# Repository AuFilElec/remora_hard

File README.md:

# remora_hard
PCB Remora v1.4 - gestionnaire de chauffage électrique

La **Remora** permet de piloter 7 zones de chauffage électrique via les fils pilotes. Mais aussi de récupérer la téléinformation de votre compteur Enedis et piloter votre ballon d'eau chaude.

**Schematic**

**PCB**

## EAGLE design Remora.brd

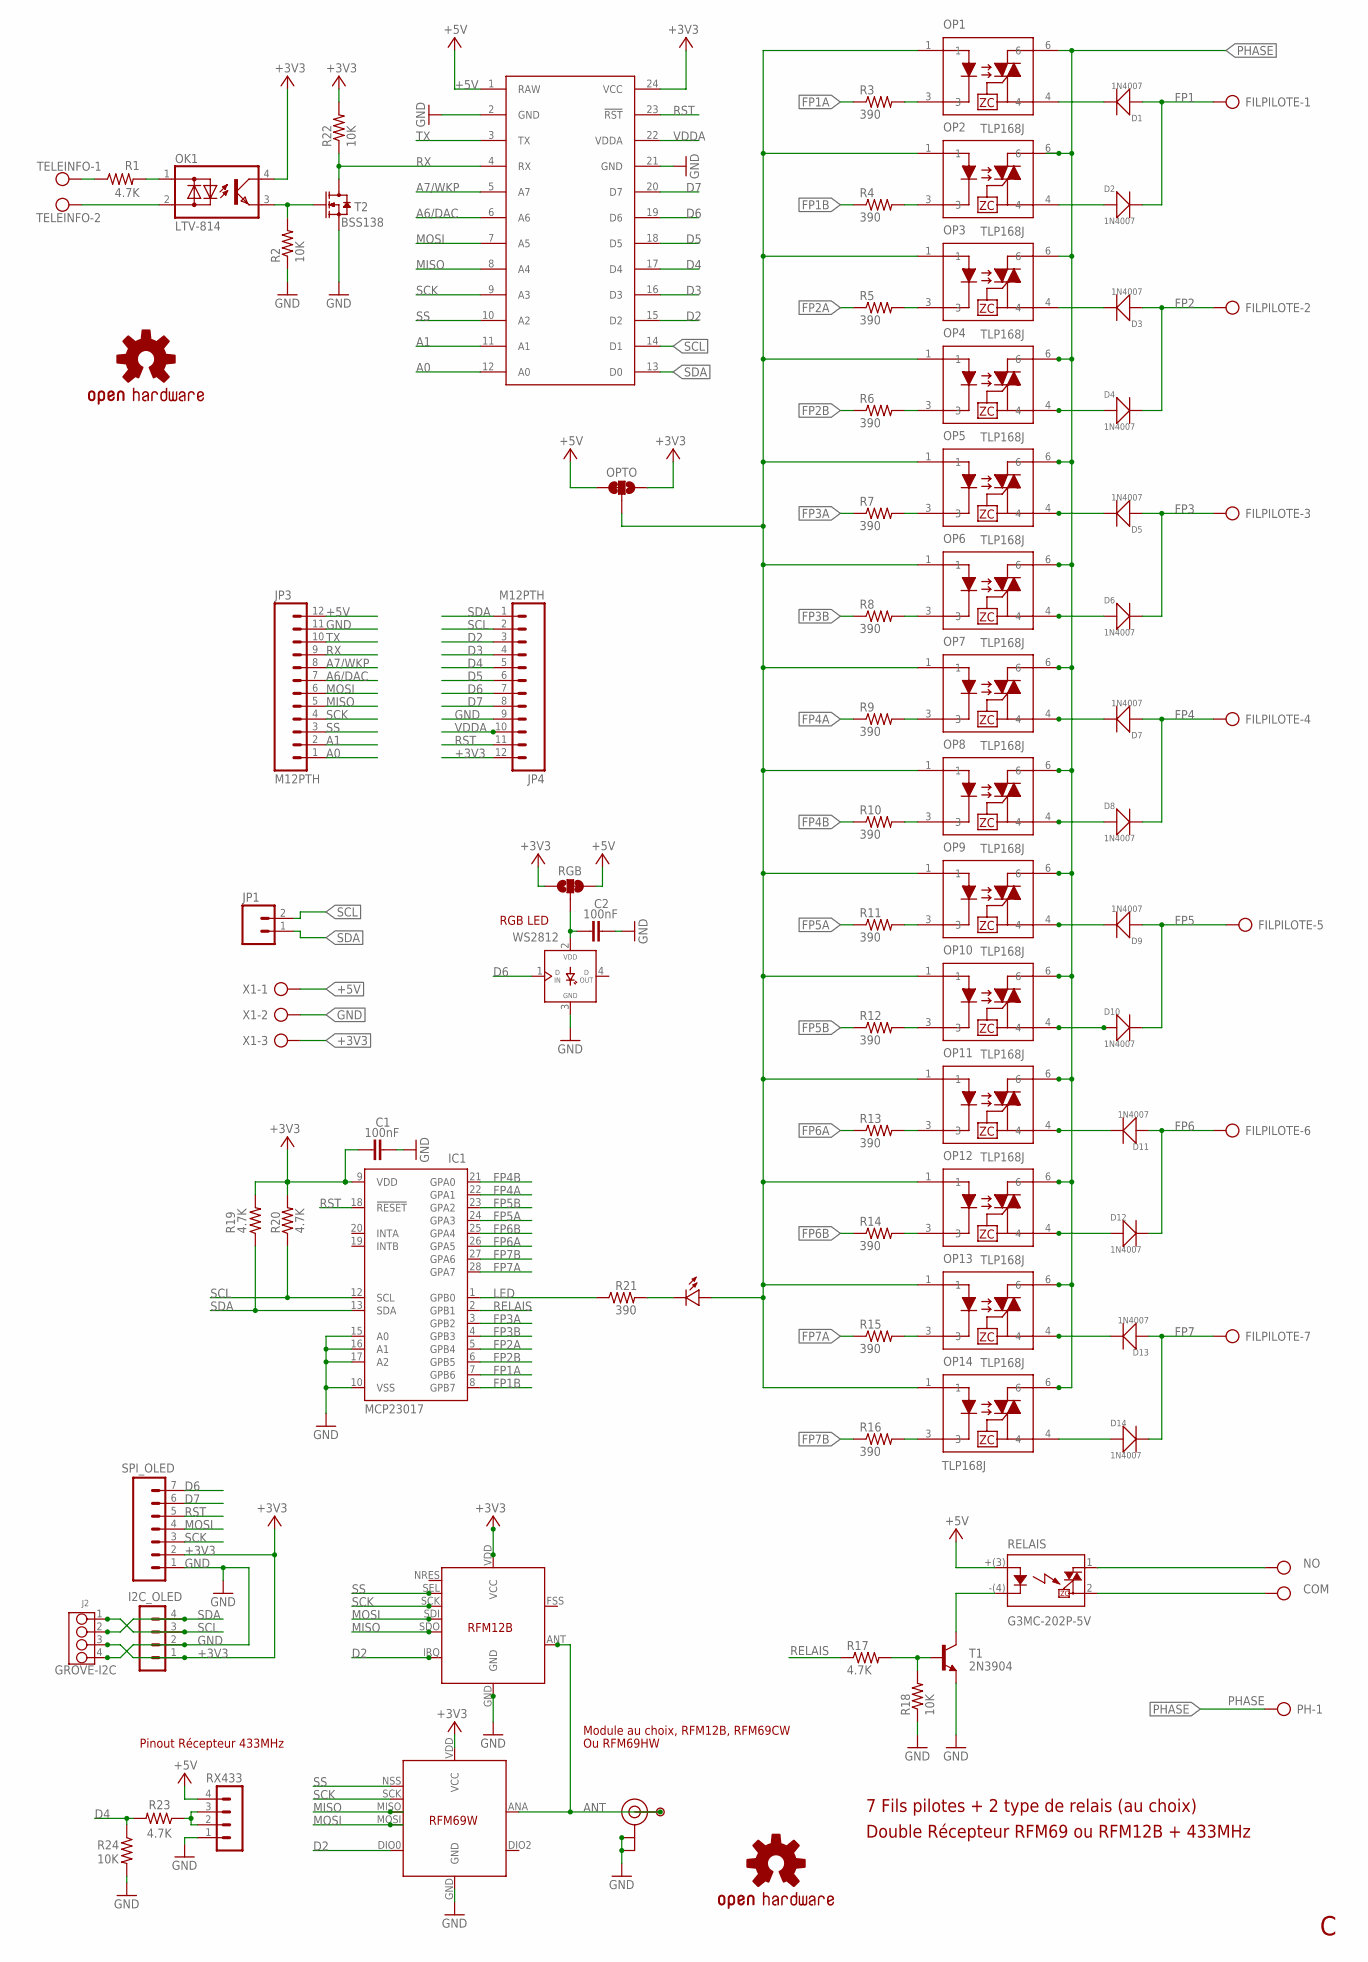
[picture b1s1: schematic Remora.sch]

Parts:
C1, C2: 100nF; 1206-CAP
D1, D2, D3, D4, D5, D6, D7, D8, D9, D10, D11, D12, D13, D14: 1N4007; DO-214AC
FILPILOTE: AK500/7
I2C_OLED: CON_HEADER_1X04'SMALL''; M1X4
IC1: MCP23017; DIL28-3
J2: GROVE-I2C; 4P-2.0
JP1: M02PTH; 1X02
JP3, JP4: M12PTH; 1X12-SMALL-PADS
LED: LED3MM
LOGO1, LOGO2: OSHW-LOGOL; OSHW-LOGO-L
OK1: LTV-814; DIL4-SMD
OP1, OP2, OP3, OP4, OP5, OP6, OP7, OP8, OP9, OP10, OP11, OP12, OP13, OP14: TLP168J; MFSOP-4-HANDSOLDER
OPTO: JUMPER-PAD-3-2OF3_NC_BY_TRACE_LARGE; PAD-JUMPER-3-2OF3_NC_BY_TRACE_YES_SILK_LARGE
P1: PADSMALL; PAD-SMALL
PARTICLE: Spark/Photon; SPARK_CORE
PH: AK500/3
R1, R17, R19, R20, R23: 4.7K; 1206-RES
R2, R18, R22, R24: 10K; 1206-RES
R3, R4, R5, R6, R7, R8, R9, R10, R11, R12, R13, R14, R15, R16, R21: 390; 1206-RES
RELAIS: G3MC-202P-5V; SIP-4
RGB: JUMPER-PAD-3-2OF3_NC_BY_TRACE_SMALL; PAD-JUMPER-3-2OF3_NC_BY_TRACE_YES_SILK_FULL_BOX
RX433: CON_HEADER_1X04'NO_LOCK'; 1X04_NO_LOCK
SPI_OLED: CON_HEADER_1X07'SMALL'; M1X7
T1: 2N3904; TO92-EBC
T2: BSS138; SOT23
TELEINFO: AK500/2
U$2: RFM12B; RFM12B-MINPADS
U$3: RFM69W; RFM69W-MINPADS
U-FL: U.FL
WS2812: RGB LED; WS2812-PTH
X1: AK500/3

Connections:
+3V3: C1.1, I2C_OLED.1, IC1.9 (VDD), J2.3, JP4.12, OK1.4 (C), OPTO.1, PARTICLE.24 (VCC), R19.2, R20.2, R22.2, RGB.1, SPI_OLED.2, U$2.VDD (VCC), U$3.VDD (VCC), X1.3
+5V: JP3.12, OPTO.3, PARTICLE.1 (RAW), RELAIS.+(3) (3), RGB.3, RX433.4, X1.1
A0: JP3.1, PARTICLE.12 (A0)
A1: JP3.2, PARTICLE.11 (A1)
A6/DAC: JP3.7, PARTICLE.6 (A6)
A7/WKP: JP3.8, PARTICLE.5 (A7)
ANT: P1.1, U$2.ANT, U$3.ANA (ANT), U-FL.3 (SIGNAL)
COM: PH.3, RELAIS.2
D2: JP4.3, PARTICLE.15 (D2), U$2.IRQ, U$3.DIO0
D3: JP4.4, PARTICLE.16 (D3)
D4: JP4.5, PARTICLE.17 (D4), R23.2, R24.1
D5: JP4.6, PARTICLE.18 (D5)
D6: JP4.7, PARTICLE.19 (D6), SPI_OLED.7, WS2812.1 (DIN)
D7: JP4.8, PARTICLE.20 (D7), SPI_OLED.6
FP1: D1.1 (+), D2.2 (-), FILPILOTE.1
FP1A: IC1.7 (GPB6), R3.1
FP1B: IC1.8 (GPB7), R4.1
FP2: D3.1 (+), D4.2 (-), FILPILOTE.2
FP2A: IC1.5 (GPB4), R5.1
FP2B: IC1.6 (GPB5), R6.1
FP3: D5.1 (+), D6.2 (-), FILPILOTE.3
FP3A: IC1.3 (GPB2), R7.1
FP3B: IC1.4 (GPB3), R8.1
FP4: D7.1 (+), D8.2 (-), FILPILOTE.4
FP4A: IC1.22 (GPA1), R9.1
FP4B: IC1.21 (GPA0), R10.1
FP5: D9.1 (+), D10.2 (-), FILPILOTE.5
FP5A: IC1.24 (GPA3), R11.1
FP5B: IC1.23 (GPA2), R12.1
FP6: D11.1 (+), D12.2 (-), FILPILOTE.6
FP6A: IC1.26 (GPA5), R13.1
FP6B: IC1.25 (GPA4), R14.1
FP7: D13.1 (+), D14.2 (-), FILPILOTE.7
FP7A: IC1.28 (GPA7), R15.1
FP7B: IC1.27 (GPA6), R16.1
GND: C1.2, C2.2, I2C_OLED.2, IC1.10 (VSS), IC1.15 (A0), IC1.16 (A1), IC1.17 (A2), J2.4, JP3.11, JP4.9, PARTICLE.2 (GND), PARTICLE.21 (GND), R2.1, R18.1, R24.2, RX433.1, SPI_OLED.1, T1.E, T2.2 (S), U$2.GND, U$3.GND, U-FL.1 (GND), U-FL.2 (GND), WS2812.3 (GND), X1.2
LED: IC1.1 (GPB0), R21.1
MISO: JP3.5, PARTICLE.8 (A4), U$2.SDO, U$3.MISO
MOSI: JP3.6, PARTICLE.7 (A5), SPI_OLED.4, U$2.SDI, U$3.MOSI
unnamed: D1.2 (-), OP1.4
unnamed: D2.1 (+), OP2.4
unnamed: OK1.2 (AC2), TELEINFO.2
unnamed: OK1.1 (AC1), R1.2
unnamed: R1.1, TELEINFO.1
unnamed: LED.MINUS, R21.2
unnamed: OP1.3, R3.2
unnamed: OP2.3, R4.2
unnamed: OP3.3, R5.2
unnamed: OP4.3, R6.2
unnamed: OP5.3, R7.2
unnamed: OP6.3, R8.2
unnamed: OP7.3, R9.2
unnamed: OP8.3, R10.2
unnamed: RELAIS.-(4) (4), T1.C
unnamed: C2.1, RGB.2, WS2812.2 (VDD)
unnamed: OK1.3 (E), R2.2, T2.1 (G)
unnamed: OP9.3, R11.2
unnamed: LED.PLUS, OP1.1, OP2.1, OP3.1, OP4.1, OP5.1, OP6.1, OP7.1, OP8.1, OP9.1, OP10.1, OP11.1, OP12.1, OP13.1, OP14.1, OPTO.2
unnamed: R17.2, R18.2, T1.B
unnamed: D3.2 (-), OP3.4
unnamed: D5.2 (-), OP5.4
unnamed: D4.1 (+), OP4.4
unnamed: D7.2 (-), OP7.4
unnamed: D6.1 (+), OP6.4
unnamed: D8.1 (+), OP8.4
unnamed: OP10.3, R12.2
unnamed: OP14.3, R16.2
unnamed: D9.2 (-), OP9.4
unnamed: OP11.3, R13.2
unnamed: OP12.3, R14.2
unnamed: D10.1 (+), OP10.4
unnamed: D12.1 (+), OP12.4
NO: PH.2, RELAIS.1
PHASE: OP1.6, OP2.6, OP3.6, OP4.6, OP5.6, OP6.6, OP7.6, OP8.6, OP9.6, OP10.6, OP11.6, OP12.6, OP13.6, OP14.6, PH.1
RELAIS: IC1.2 (GPB1), R17.1
RST: IC1.18 (!RESET), JP4.11, PARTICLE.23 (!RST), SPI_OLED.5
RX: JP3.9, PARTICLE.4 (RX), R22.1, T2.3 (D)
RX433: R23.1, RX433.2, RX433.3
S$1: D11.2 (-), OP11.4
S$3: D13.2 (-), OP13.4
S$5: OP13.3, R15.2
S$11: D14.1 (+), OP14.4
SCK: JP3.4, PARTICLE.9 (A3), SPI_OLED.3, U$2.SCK, U$3.SCK
SCL: I2C_OLED.3, IC1.12 (SCL), J2.1, JP1.2, JP4.2, PARTICLE.14 (D1), R20.1
SDA: I2C_OLED.4, IC1.13 (SDA), J2.2, JP1.1, JP4.1, PARTICLE.13 (D0), R19.1
SS: JP3.3, PARTICLE.10 (A2), U$2.SEL, U$3.NSS (SEL)
TX: JP3.10, PARTICLE.3 (TX)
VDDA: JP4.10, PARTICLE.22 (VDDA)

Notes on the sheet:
7 Fils pilotes + 2 type de relais (au choix)
Module au choix, RFM12B, RFM69CW
Ou RFM69HW
Pinout Récepteur 433MHz
Double Récepteur RFM69 ou RFM12B + 433MHz
RGB LED

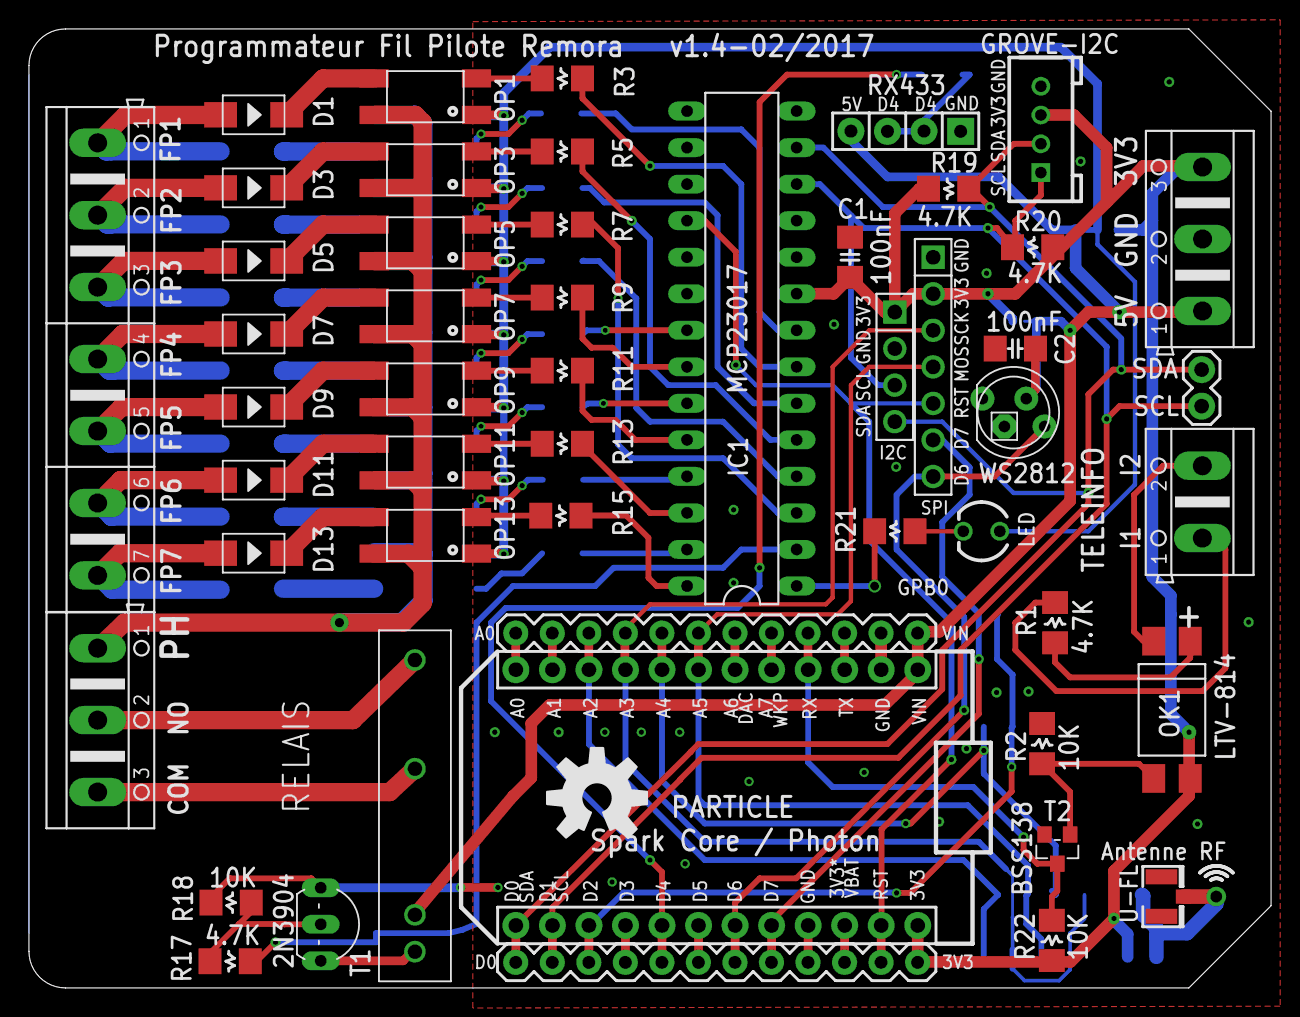
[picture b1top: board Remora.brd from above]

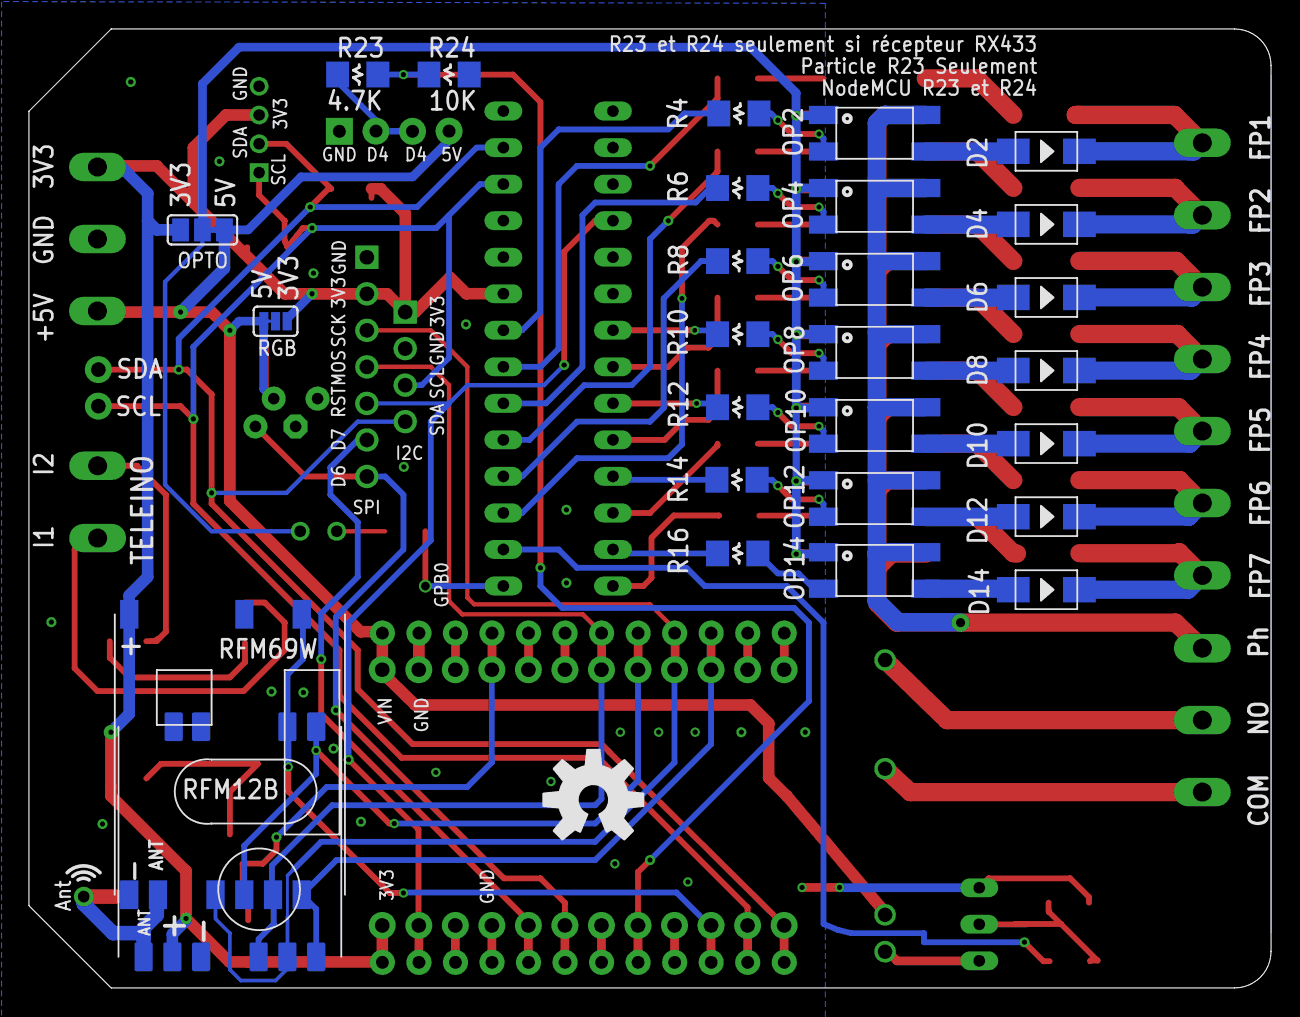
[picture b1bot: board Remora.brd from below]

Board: 2 copper layers, 86.4 x 66.7 mm, 81 parts (28 on the bottom side), 88 nets.

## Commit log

2017-01-03 Ajout de la nouvelle version de la board Remora v1.4
2017-01-03 Mise à jour du PCB et ajout d'images
2017-01-03 Ajout des images du schéma et du PCB de la Remora
2017-02-25 Correction d'une anomalie de connexion de la LED rouge
2017-02-26 Correction d'anomalie sur la route de la LED
2017-02-26 Mise à jour de l'image du PCB
2017-02-26 Correction d'anomalie de la route de la phase
2017-02-26 Modification de la Remora pour accepter directement un Wemos D1 mini sur headers
2017-02-26 Mise à jour de l'image du schéma
2017-02-26 Mise à jour du numéro de version du PCB
2017-02-26 Suppression d'une valeur inutile
2017-02-26 Mise à jour des values
2017-02-27 Modification pour export gerbers
2017-02-27 Correction d'une erreur dans la couche dimension
2017-08-21 Update description README

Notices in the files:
parts and their libraries:
microbuilder: This work is placed in the public domain, and may be freely used for commercial and non-commercial work with the following conditions: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
SparkFun-Aesthetics: Licensing: Creative Commons ShareAlike 4.0 International - https://creativecommons.org/licenses/by-sa/4.0
